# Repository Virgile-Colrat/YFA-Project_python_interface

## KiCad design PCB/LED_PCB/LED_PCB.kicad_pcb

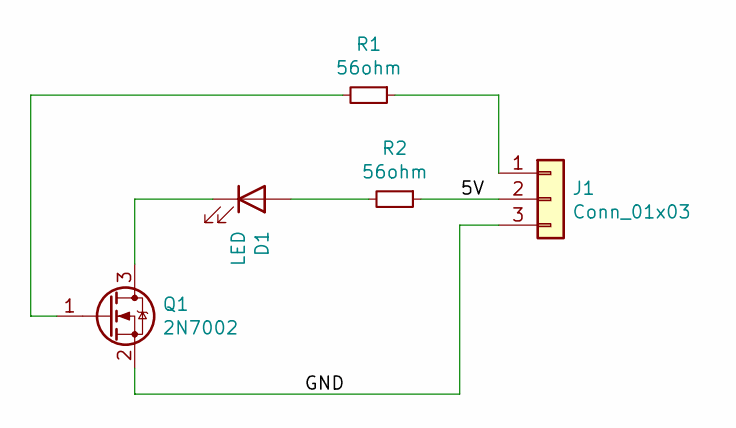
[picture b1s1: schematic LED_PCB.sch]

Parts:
D1: LED; LED_Cree-XB
J1: Conn_01x03; PinHeader_1x03_P2.54mm_Vertical
Q1: 2N7002; SOT-23
R1, R2: 56ohm; R_0805_2012Metric

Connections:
/5V: J1.2, R2.1
/GND: J1.3, Q1.2 (S)
unnamed: D1.1 (K), Q1.3 (D)
unnamed: D1.2 (A), R2.2
unnamed: J1.1, R1.1
unnamed: Q1.1 (G), R1.2

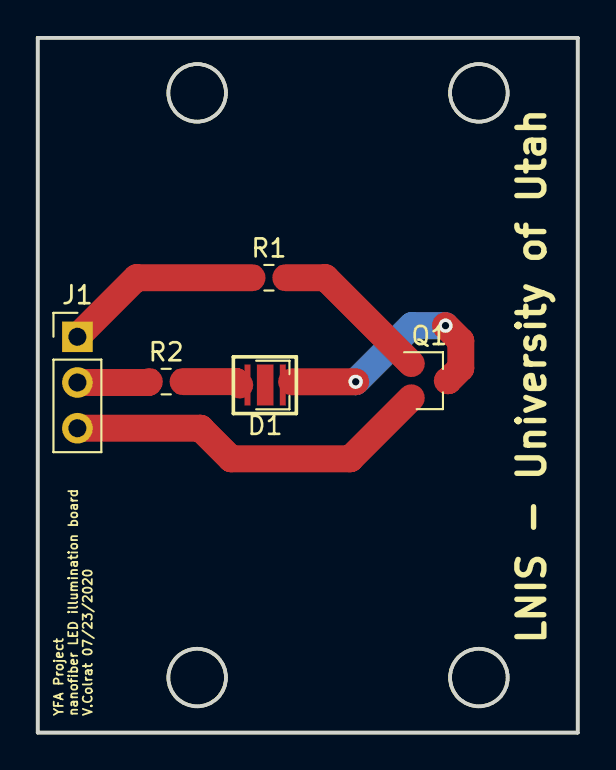
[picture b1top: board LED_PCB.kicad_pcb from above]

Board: 2 copper layers, 30.0 x 38.6 mm, 5 parts (0 on the bottom side), 6 nets.

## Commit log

2020-05-18 1st update of main
2020-05-19 updated main
2020-05-19 Updated omegaette protocol doc
2020-05-19 project reorganised
2020-05-19 Serial communication added
2020-05-20 Omegaette control working
2020-05-20 3D model added
2020-05-20 MFC documentation added
2020-05-21 EOD backup
2020-05-21 backup
2020-05-22 updated documentation
2020-05-26 backup-small changes
2020-05-28 Keithley 236 control
2020-06-02 COB documentation added
2020-06-03 keithley 236 commands added
2020-06-03 Keithley cmds added
2020-06-03 keithley cmds updated
2020-06-04 System now fully functional
2020-06-08 MFC control update
2020-06-16 full project update
2020-07-06 Full system with water bath control
2020-07-06 just backup
2020-07-14 updated Matt's chip test
2020-07-22 latest update
2020-07-27 3D model update
2020-07-28 main.py updated
2020-08-07 Measurment results added
2020-08-26 updated manua
2020-08-31 Updated 3D model, LED polarization tests
2020-09-15 noise caracterization test added
2020-09-15 Test SMU 1GOhm added
2020-09-15 updated source for smu noise
2020-09-15 updated Source nois test of SMU
